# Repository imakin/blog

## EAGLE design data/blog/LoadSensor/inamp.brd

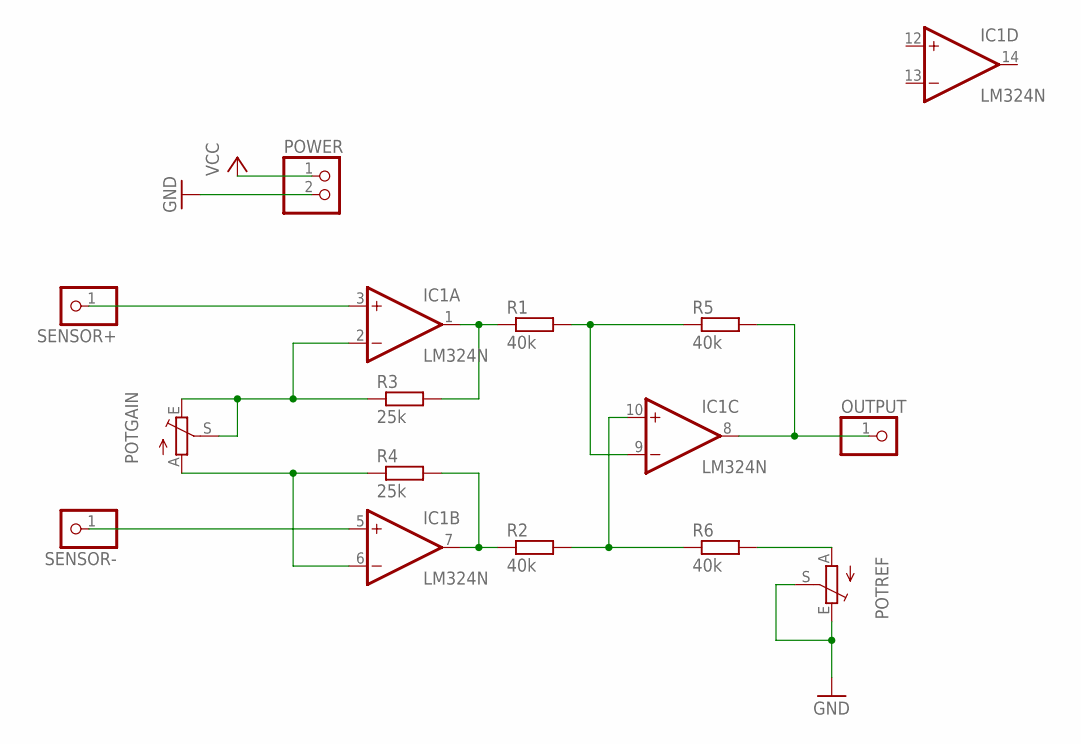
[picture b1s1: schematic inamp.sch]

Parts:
IC1: LM324N; DIL14
OUTPUT: PINHD-1X1; 1X01
POTGAIN: TRIM_EU-CA6V; CA6V
POTREF: TRIM_EU-CA6V; CA6V
POWER: PINHD-1X2; 1X02
R1, R2, R5, R6: 40k; 0204/7
R3, R4: 25k; 0204/7
SENSOR+: PINHD-1X1; 1X01
SENSOR-: PINHD-1X1; 1X01

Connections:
GND: IC1.11 (V-), POTREF.E, POTREF.S, POWER.2
unnamed: IC1.1 (OUT), R1.1, R3.2
unnamed: IC1.7 (OUT), R2.1, R4.2
unnamed: IC1.9 (-IN), R1.2, R5.1
unnamed: IC1.10 (+IN), R2.2, R6.1
unnamed: IC1.2 (-IN), POTGAIN.E, POTGAIN.S, R3.1
unnamed: IC1.6 (-IN), POTGAIN.A, R4.1
unnamed: POTREF.A, R6.2
unnamed: IC1.8 (OUT), OUTPUT.1, R5.2
unnamed: IC1.5 (+IN), SENSOR-.1
SENSOR+: IC1.3 (+IN), SENSOR+.1
VCC: IC1.4 (V+), POWER.1

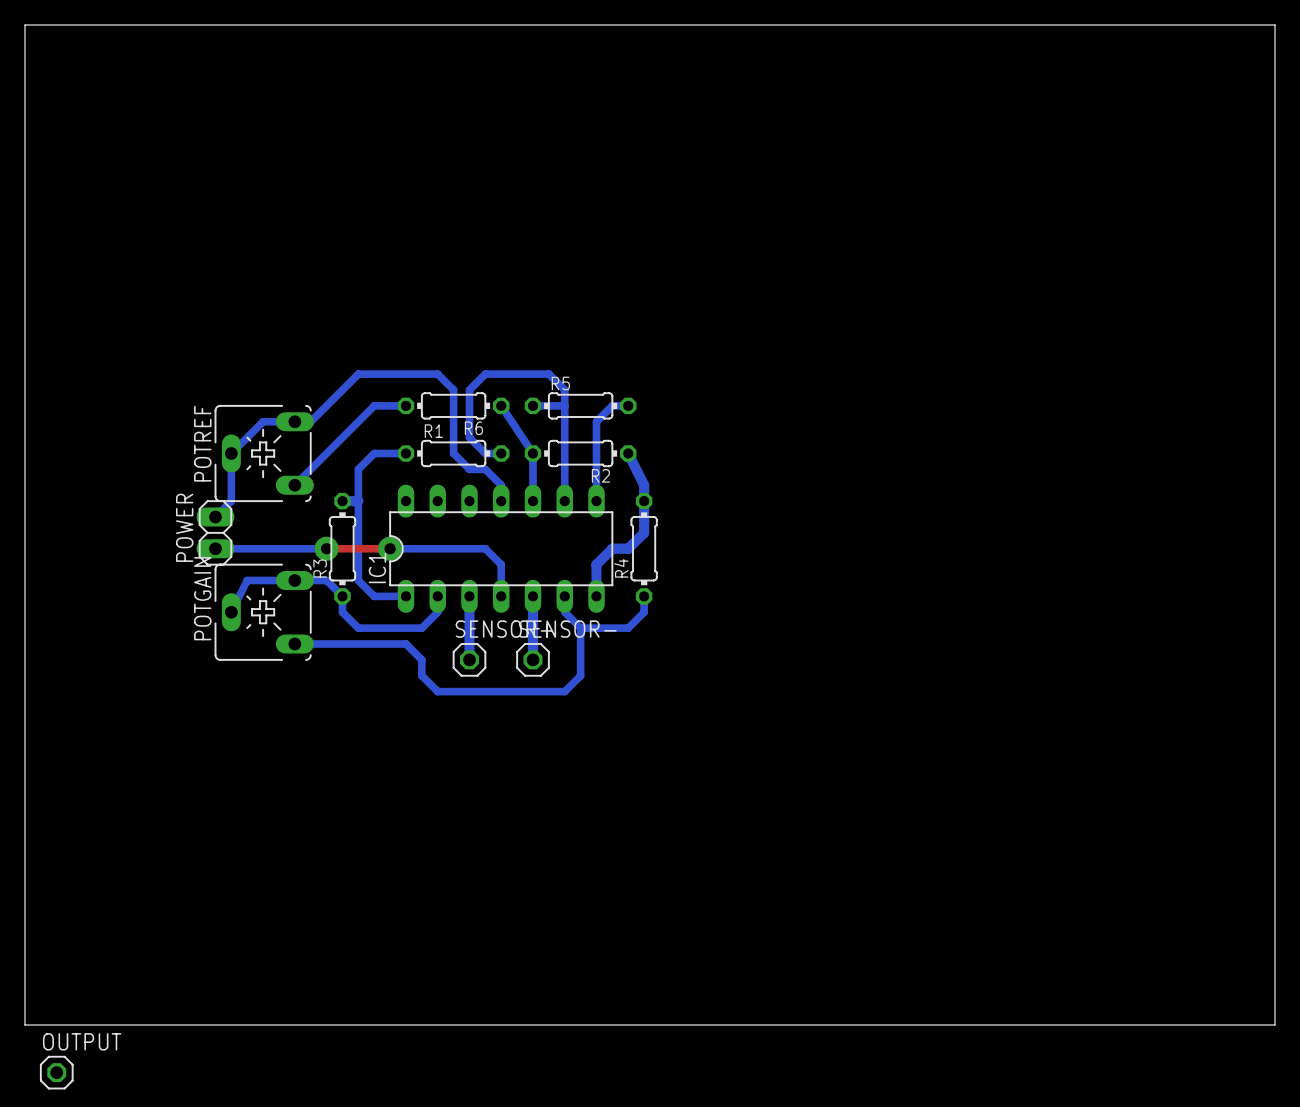
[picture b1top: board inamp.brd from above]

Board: 2 copper layers, 100.0 x 80.0 mm, 13 parts (0 on the bottom side), 12 nets.

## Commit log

2015-03-31 added all file
2015-04-01 chmod
2015-04-02 support site & local devel directory
2015-04-02 templateDir fetching at startup only
2015-04-02 added files for load sensor
2015-04-02 added loadsensor to blog
2015-04-15 new file: blog_Dota2.html
2015-04-24 rm eagle
2015-04-24 kabeh yo ben
2015-04-25 keep what compatible only tho
